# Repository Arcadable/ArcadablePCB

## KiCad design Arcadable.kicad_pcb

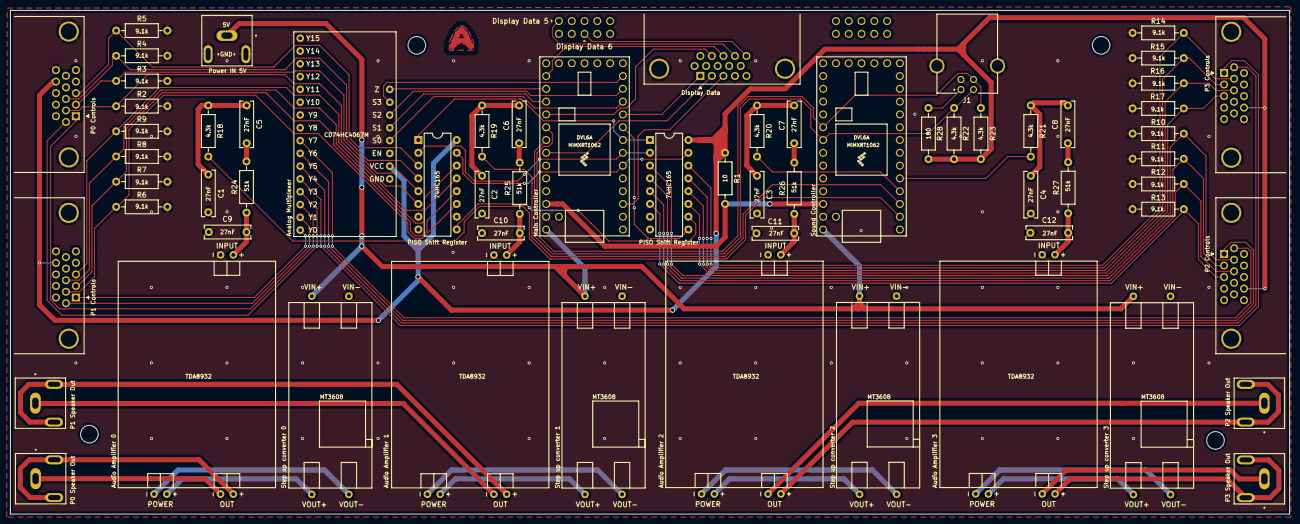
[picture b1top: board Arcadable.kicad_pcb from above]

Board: 2 copper layers, 254.0 x 100.0 mm, 64 parts (0 on the bottom side), 80 nets.

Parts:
Analog_Multiplexer1: CD74HC4067M; multiplexer
Audio_Amplifier_1, Audio_Amplifier_2, Audio_Amplifier_3, Audio_Amplifier_4: TDA8932T; amplifier
C1, C2, C3, C4, C5, C6, C7, C8, C9, C10, C11, C12: 27nF; C_Rect_L9.0mm_W2.5mm_P7.50mm_MKT
Controller_Main1: Teensy4.0; Teensy40
Controller_Sound1: Teensy4.0; Teensy40
Display_Data1: DB15_Female_HighDensity; DSUB-15-HD_Female_Horizontal_P2.29x1.98mm_EdgePinOffset8.35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
J1: 292304-1; TE_292304-1
J2, J3, J4, J5, J6: PJRAN1X1U02AUX; SWITCHCRAFT_PJRAN1X1U02AUX
P0_Controls1, P1_Controls1, P2_Controls1, P3_Controls1: DB15_Female_HighDensity; DSUB-15-HD_Female_Horizontal_P2.29x1.98mm_EdgePinOffset8.35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
R1: 10; R_Axial_DIN0207_L6.3mm_D2.5mm_P10.16mm_Horizontal
R2, R3, R4, R5, R6, R7, R8, R9, R10, R11, R12, R13, R14, R15, R16, R17: 9.1k; R_Axial_DIN0207_L6.3mm_D2.5mm_P10.16mm_Horizontal
R18, R19, R20, R21, R22, R23: 4.3k; R_Axial_DIN0207_L6.3mm_D2.5mm_P10.16mm_Horizontal
R24, R25, R26, R27: 51k; R_Axial_DIN0207_L6.3mm_D2.5mm_P10.16mm_Horizontal
R28: 180; R_Axial_DIN0207_L6.3mm_D2.5mm_P10.16mm_Horizontal
Step_Up_Converter_1, Step_Up_Converter_2, Step_Up_Converter_3, Step_Up_Converter_4: MT3608; stepup
U1, U2: 74HC165; DIP-16_W7.62mm

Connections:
3.3v: Analog_Multiplexer1.24, P0_Controls1.14, P1_Controls1.14, P2_Controls1.14, P3_Controls1.14, R1.1, R22.2, R23.2, R28.1, U1.16, U2.16
3.3v_Pre: Controller_Main1.31, Controller_Sound1.31, R1.2
5V: Controller_Main1.33, Controller_Sound1.33, J2.1, Step_Up_Converter_1.4, Step_Up_Converter_2.4, Step_Up_Converter_3.4, Step_Up_Converter_4.4
25V-0: Audio_Amplifier_1.6, Step_Up_Converter_1.2
25V-1: Audio_Amplifier_2.6, Step_Up_Converter_2.2
25V-2: Audio_Amplifier_3.6, Step_Up_Converter_3.2
25V-3: Audio_Amplifier_4.6, Step_Up_Converter_4.2
Analog_Input: Analog_Multiplexer1.1, Controller_Main1.22
Analog_Input_Select_0: Analog_Multiplexer1.10, Controller_Main1.11
Analog_Input_Select_1: Analog_Multiplexer1.11, Controller_Main1.23
Analog_Input_Select_2: Analog_Multiplexer1.14, Controller_Main1.12
Analog_Input_Select_3: Analog_Multiplexer1.13, Controller_Main1.13
Display_Data+_0: Controller_Main1.3, Display_Data1.3
Display_Data+_1: Controller_Main1.10, Display_Data1.1
Display_Data+_2: Controller_Main1.21, Display_Data1.13
Display_Data+_3: Controller_Main1.24, Display_Data1.12
Display_Data+_4: Controller_Main1.27, Display_Data1.2
Display_Data+_5: Controller_Main1.35, Display_Data1.14
Display_Data+_6: Controller_Main1.40, Display_Data1.15
GND: Analog_Multiplexer1.12, Analog_Multiplexer1.15, Audio_Amplifier_1.3, Audio_Amplifier_2.3, Audio_Amplifier_3.3, Audio_Amplifier_4.3, C1.2, C2.2, C3.2, C4.2, C9.2, C10.2, C11.2, C12.2, Controller_Main1.32, Controller_Sound1.32, Display_Data1.0, J1.4, J1.None, J2.2, J2.3, P0_Controls1.0, P0_Controls1.15, P1_Controls1.0, P1_Controls1.15, P2_Controls1.0, P2_Controls1.15, P3_Controls1.0, P3_Controls1.15, R2.2, R3.2, R4.2, R5.2, R6.2, R7.2, R8.2, R9.2, R10.2, R11.2, R12.2, R13.2, R14.2, R15.2, R16.2, R17.2, Step_Up_Converter_1.3, Step_Up_Converter_2.3, Step_Up_Converter_3.3, Step_Up_Converter_4.3, U1.8, U2.8
GND-0: Audio_Amplifier_1.5, Step_Up_Converter_1.1
GND-1: Audio_Amplifier_2.5, Step_Up_Converter_2.1
GND-2: Audio_Amplifier_3.5, Step_Up_Converter_3.1
GND-3: Audio_Amplifier_4.5, Step_Up_Converter_4.1
I2C_SCL0: Controller_Main1.26, Controller_Sound1.26, J1.2, R22.1
I2C_SDA0: Controller_Main1.25, Controller_Sound1.25, J1.3, R23.1
unnamed: Audio_Amplifier_1.4, C9.1, R24.1
unnamed: Audio_Amplifier_2.4, C10.1, R25.1
unnamed: Audio_Amplifier_3.4, C11.1, R26.1
unnamed: Audio_Amplifier_4.4, C12.1, R27.1
unnamed: C1.1, C5.1, R18.1
unnamed: C2.1, C6.1, R19.1
unnamed: C3.1, C7.1, R20.1
unnamed: C4.1, C8.1, R21.1
unnamed: C5.2, R24.2
unnamed: C6.2, R25.2
unnamed: C7.2, R26.2
unnamed: C8.2, R27.2
unnamed: J1.1, R28.2
unnamed: U1.9, U2.10
P0_Button_0: P0_Controls1.7, R2.1, U1.6
P0_Button_1: P0_Controls1.2, R3.1, U1.5
P0_Button_2: P0_Controls1.8, R4.1, U1.4
P0_Button_3: P0_Controls1.3, R5.1, U1.3
P0_Joystick_X: Analog_Multiplexer1.6, P0_Controls1.6
P0_Joystick_Y: Analog_Multiplexer1.7, P0_Controls1.1
P0_Speaker_Output+: Audio_Amplifier_1.2, J5.2, J5.3
P0_Speaker_Output-: Audio_Amplifier_1.1, J5.1
P0_Speaker_Signal: Controller_Sound1.2, R18.2
P1_Button_0: P1_Controls1.7, R6.1, U1.11
P1_Button_1: P1_Controls1.2, R7.1, U1.12
P1_Button_2: P1_Controls1.8, R8.1, U1.13
P1_Button_3: P1_Controls1.3, R9.1, U1.14
P1_Joystick_X: Analog_Multiplexer1.8, P1_Controls1.6
P1_Joystick_Y: Analog_Multiplexer1.9, P1_Controls1.1
P1_Speaker_Output+: Audio_Amplifier_2.2, J3.2, J3.3
P1_Speaker_Output-: Audio_Amplifier_2.1, J3.1
P1_Speaker_Signal: Controller_Sound1.3, R19.2
P2_Button_0: P2_Controls1.7, R10.1, U2.3
P2_Button_1: P2_Controls1.2, R11.1, U2.4
P2_Button_2: P2_Controls1.8, R12.1, U2.5
P2_Button_3: P2_Controls1.3, R13.1, U2.6
P2_Joystick_X: Analog_Multiplexer1.2, P2_Controls1.6
P2_Joystick_Y: Analog_Multiplexer1.3, P2_Controls1.1
P2_Speaker_Output+: Audio_Amplifier_3.2, J4.2, J4.3
P2_Speaker_Output-: Audio_Amplifier_3.1, J4.1
P2_Speaker_Signal: Controller_Sound1.4, R20.2
P3_Button_0: P3_Controls1.7, R14.1, U2.14
P3_Button_1: P3_Controls1.2, R15.1, U2.13
P3_Button_2: P3_Controls1.8, R16.1, U2.12
P3_Button_3: P3_Controls1.3, R17.1, U2.11
P3_Joystick_X: Analog_Multiplexer1.4, P3_Controls1.6
P3_Joystick_Y: Analog_Multiplexer1.5, P3_Controls1.1
P3_Speaker_Output+: Audio_Amplifier_4.2, J6.2, J6.3
P3_Speaker_Output-: Audio_Amplifier_4.1, J6.1
P3_Speaker_Signal: Controller_Sound1.5, R21.2
Reg_Clock_Inhibit: Controller_Main1.6, U1.15, U2.15
Reg_Clock_Input: Controller_Main1.7, U1.2, U2.2
Reg_Serial_Output: Controller_Main1.9, U2.9
Reg_Shift_Load: Controller_Main1.8, U1.1, U2.1

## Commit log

2021-05-25 init
